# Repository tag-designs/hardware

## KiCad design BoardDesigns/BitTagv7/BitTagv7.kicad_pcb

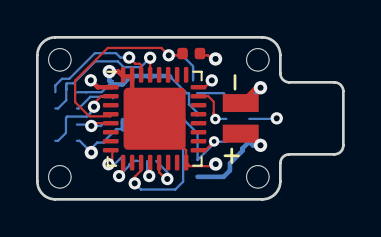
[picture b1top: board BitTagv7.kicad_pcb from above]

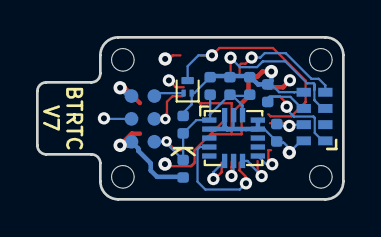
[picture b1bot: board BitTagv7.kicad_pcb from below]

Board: 4 copper layers, 17.0 x 9.0 mm, 18 parts (11 on the bottom side), 16 nets.

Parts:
C402, C403, C501, C502, C503: 0.1uf; C_0402_1005Metric
C404: 4.7uf; C_0402_1005Metric
D401: D; D_0402_1005Metric
J201: CONN_02X04; tagpoints6
J301, J302, J303, J304: Conn_01x01; taghole1.25mm
J401: CONN_01X02; MS621
Q501: Q_NPN_BEC; SOT-883
R1: 10k; R_0402_1005Metric
U302: stm32l432; QFN-32-1EP_5x5mm_P0.5mm_EP3.45x3.45mm
U405: adxl362; ADXL362
U501: RV-3028-C7; RV-8803-C7

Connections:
/SCL: U302.29, U501.3
/SDA: U302.30, U501.4
/clkout: U302.2, U501.1
ACCEL_CS: U302.9, U405.8
GND: C402.2, C403.2, C404.2, C501.2, C502.2, C503.2, J201.6, J401.2, Q501.2, R1.2, U302.16, U302.31, U302.32, U302.33, U405.2, U405.12, U405.13, U405.15, U405.16, U501.5, U501.8
unnamed: C502.1, Q501.3, U302.4
unnamed: R1.1, U501.6
RST: J201.5, Q501.1
SENS_MISO: U302.12, U405.7
SENS_MOSI: U302.13, U405.6
SENS_SCLK: U302.11, U405.4
SWCLK: J201.4, U302.24
SWDIO: J201.3, U302.23
VBAT: D401.2, J201.2, J401.1
VIN: C402.1, C403.1, C404.1, C501.1, C503.1, D401.1, J201.1, U302.1, U302.5, U302.17, U405.1, U405.14, U501.7
WKUP4: U302.8, U405.9

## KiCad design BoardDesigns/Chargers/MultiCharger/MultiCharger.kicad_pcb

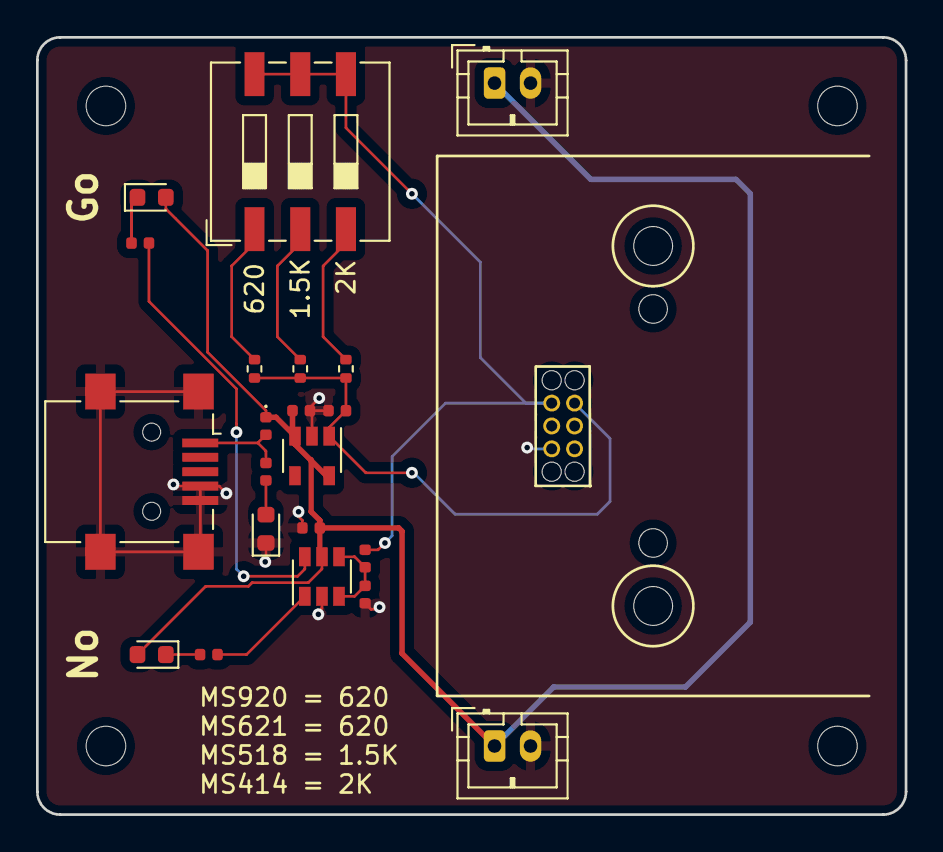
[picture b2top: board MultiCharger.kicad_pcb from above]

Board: 2 copper layers, 48.3 x 43.2 mm, 26 parts (0 on the bottom side), 14 nets.

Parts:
C101: 0.1uF; C_0402_1005Metric
C106: 1uF; C_0402_1005Metric
C107: 2.2uF; C_0402_1005Metric
D101: No Go; LED_0603_1608Metric
D102: LED; LED_0603_1608Metric
D103: Go; LED_0603_1608Metric
D104: D; D_0402_1005Metric
J101, J102: Conn_01x02; JST_PH_B2B-PH-K_1x02_P2.00mm_Vertical
J103: Tagbase; 6pin_tagpoints_new_offset
J104: USB_B_Mini; USB_Mini-B_Lumberg_2486_01_Horizontal
MK101, MK102, MK103, MK104: Mounting_Hole; MountingHole_2.2mm_M2
R1: 620; R_0402_1005Metric
R101, R102, R105: 1K; R_0402_1005Metric
R103: 910K; R_0402_1005Metric
R104: 130K; R_0402_1005Metric
R106: 1500; R_0402_1005Metric
R107: 2000; R_0402_1005Metric
SW101: SW_DIP_x03; SW_DIP_SPSTx03_Slide_9.78x9.8mm_W8.61mm_P2.54mm
U101: TLV6700; SOT-23-6
U106: TLV70A933_SOT23-5; SOT-23-5

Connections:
+3V3: C107.1, J103.5, R1.2, R106.2, R107.2, U106.1
/VIN: C101.1, C106.1, D101.2, D103.2, D104.1, J101.1, J102.1, U101.5, U106.3, U106.5
/Vsense: R103.2, R104.1, U101.3, U101.4
GND: C101.2, C106.2, C107.2, D102.1, J101.2, J102.2, J103.2, J104.4, J104.5, J104.6, R104.2, U101.2, U106.2
unnamed: D101.1, R101.2
unnamed: D102.2, R102.2
unnamed: D103.1, R105.2
unnamed: D104.2, J104.1, R102.1
unnamed: R1.1, SW101.1
unnamed: R101.1, U101.1
unnamed: R105.1, U101.6
unnamed: R106.1, SW101.2
unnamed: R107.1, SW101.3
TAG_VBAT: J103.6, R103.1, SW101.4, SW101.5, SW101.6

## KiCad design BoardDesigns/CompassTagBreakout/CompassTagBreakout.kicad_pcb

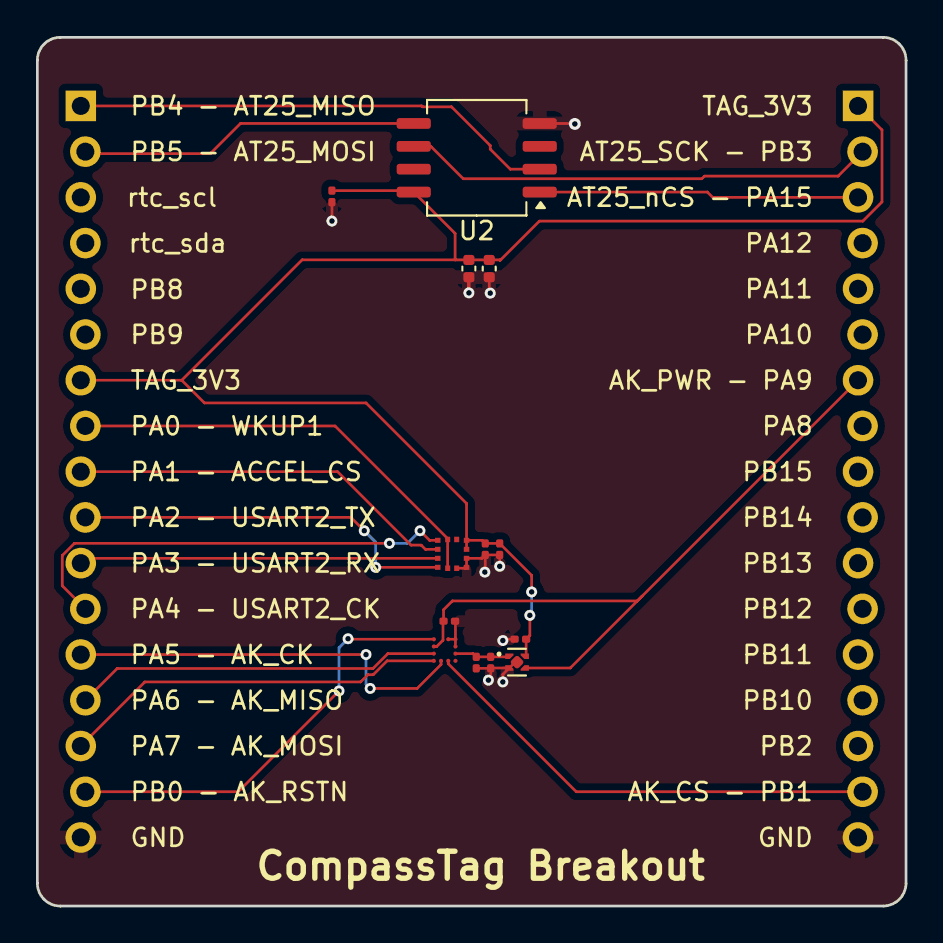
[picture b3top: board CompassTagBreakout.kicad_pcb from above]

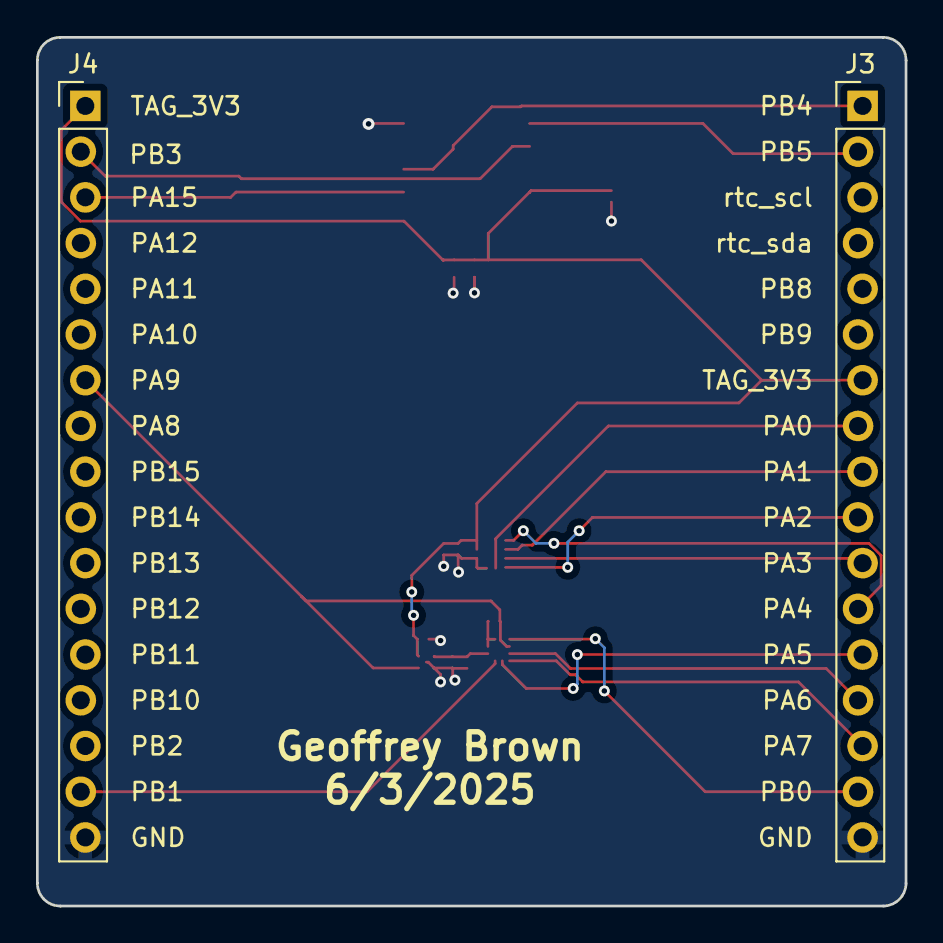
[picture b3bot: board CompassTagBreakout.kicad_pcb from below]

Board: 2 copper layers, 48.3 x 48.3 mm, 15 parts (2 on the bottom side), 18 nets.

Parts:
C3, C4, C9: 1uf; C_0201_0603Metric
C5, C6, C7, C8: 0.1uf; C_0201_0603Metric
C10, C11: 22uf; C_0402_1005Metric
J3, J4: Conn_01x17; PinHeader_1x17_P2.54mm_Vertical_Staggered
U1: TPS7A2018PDQN; Texas_X2SON-4_1x1mm_P0.65mm
U2: AT25XE321; SO-8_5.3x6.2mm_P1.27mm
U3: AK09940A; AK09940a
U4: LIS2DU12TR; LGA-12L_LIS2DU12_STM

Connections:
+1V8: C4.1, C5.1, U1.1 (OUT), U3.B1 (VDD)
/ACCEL_CS: J3.9, U4.2 (CS)
/AK_CK: J3.13, U3.A3 (SCL/SK)
/AK_CS: J4.16, U3.A2 (CSB)
/AK_MISO: J3.14, U3.B4 (SO)
/AK_MOSI: J3.15, U3.A4 (SDA/SI)
/AK_PWR: C6.1, J4.7, U1.3 (EN), U3.C4 (VOD)
/AK_RSTN: J3.16, U3.D4 (RSTN)
/AT25_MISO: J3.1, U2.2 (SIO1)
/AT25_MOSI: J3.2, U2.5 (SIO0)
/AT25_SCK: J4.2, U2.6 (SCLK)
/AT25_nCS: J4.3, U2.1 (nCS)
/TAG_3V3: C3.1, C7.1, C8.1, C9.1, C10.1, C11.1, J3.7, J4.1, U1.4 (IN), U2.8 (VCC), U4.9 (VDD), U4.10 (VDD_IO)
/USART2_CK: J3.12, U4.1 (SCL/SPC)
/USART2_RX: J3.11, U4.3 (SDO/SA0)
/USART2_TX: J3.10, U4.4 (SDA/SDI/SDO)
/WKUP1: J3.8, U4.5 (NC), U4.12 (INT1)
GND: C3.2, C4.2, C5.2, C6.2, C7.2, C8.2, C9.2, C10.2, C11.2, J3.17, J4.17, U1.2 (GND), U1.5 (Pad), U2.4 (GND), U3.C1 (VSS), U3.D1 (CAD0), U3.D2 (CAD1), U4.6 (GND), U4.7 (RES), U4.8 (GND)

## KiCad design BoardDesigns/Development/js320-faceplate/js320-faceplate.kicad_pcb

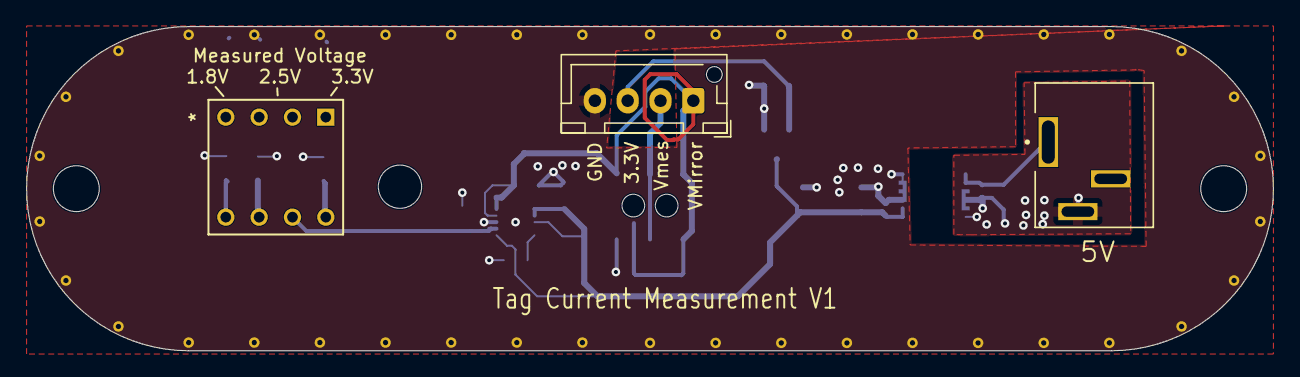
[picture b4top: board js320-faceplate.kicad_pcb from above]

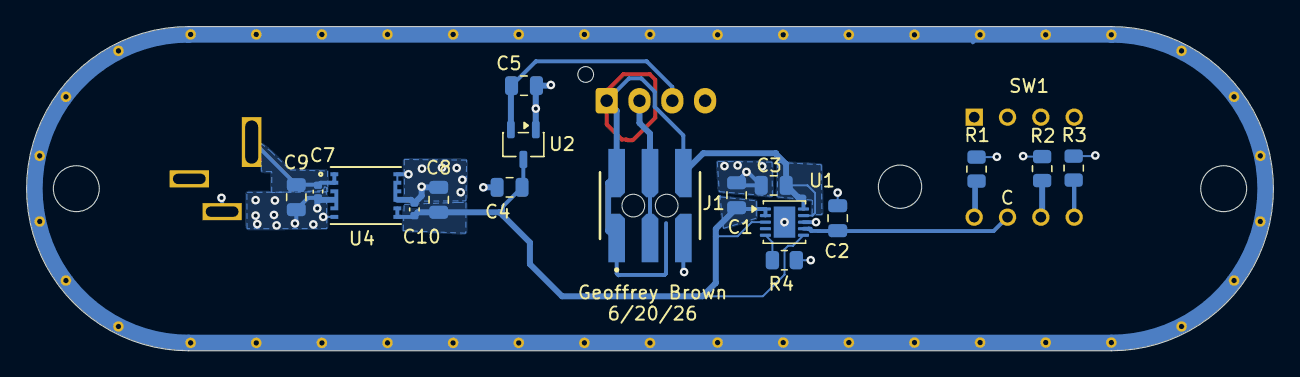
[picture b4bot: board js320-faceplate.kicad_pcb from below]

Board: 2 copper layers, 95.0 x 24.7 mm, 20 parts (16 on the bottom side), 12 nets.

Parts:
C1, C4, C5: 4.7uf; C_0805_2012Metric
C2: 470nf; C_0805_2012Metric
C3, C9: 10uf; C_0805_2012Metric
C7, C10: 22nf; C_0402_1005Metric
C8: 22uf; C_0805_2012Metric
J1: JS220
J3: Conn_01x04_Socket; JST_XH_B4B-XH-AM_1x04_P2.50mm_Vertical
J4: 54-00286; TENSILITY_54-00286
R1: 18k; R_0805_2012Metric
R2: 24k; R_0805_2012Metric
R3: 33k; R_0805_2012Metric
R4: 1k; R_0805_2012Metric
SW1: SS-10-23NPE; SS-10-23-NP_NDC
U1: LT3045xDD; DFN-10-1EP_3x3mm_P0.5mm_EP1.65x2.38mm
U2: XC6206PxxxMR; SOT-23-3
U4: PUCC33420RAQR; VSON-FCRLF12_RAQ_TEX

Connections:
+3.3V: C5.1, J3.3, U2.2 (VO)
/VINP: C7.1, C9.1, J4.A, U4.1 (EN/FLT), U4.2 (VINP)
/Vmeasure: J1.3 (I-), J1.4 (I-), J3.2
/Vprog: C3.1, J1.1 (I+), J1.2 (I+), J1.6 (V+), J3.1, U1.9 (OUTS), U1.10 (OUT)
/sens: C2.1, SW1.CB, U1.7 (SET)
/vin: C1.1, C4.1, C8.1, C10.1, U1.1 (IN), U1.2 (IN), U1.3 (EN/UV), U1.6 (PGFB), U2.3 (VI), U4.7 (SEL), U4.8 (VCC)
GND: C1.2, C2.2, C3.2, C4.2, C5.2, C8.2, C10.2, J1.5 (V-), J1.7 (SHIELD), J3.4, R1.2, R2.2, R3.2, R4.1, U1.8 (GND), U1.11 (GND), U2.1 (GND), U4.9 (GNDS), U4.10 (GNDS), U4.11 (GNDS), U4.12 (GNDS)
GNDPWR: C7.2, C9.2, J4.B, U4.3 (GNDP), U4.4 (GNDP), U4.5 (GNDP), U4.6 (GNDP)
unnamed: R1.1, SW1.1B
unnamed: R2.1, SW1.2B
unnamed: R3.1, SW1.3B
unnamed: R4.2, U1.5 (ILIM)

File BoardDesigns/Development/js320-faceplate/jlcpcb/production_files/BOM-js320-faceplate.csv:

Comment,Designator,Footprint,LCSC,Quantity
10uf,"C3,C9",C_0805_2012Metric,C15850,2
18k,R1,R_0805_2012Metric,C351602,1
1k,R4,R_0805_2012Metric,C17513,1
22nf,"C10,C7",C_0402_1005Metric,C1532,2
22uf,C8,C_0805_2012Metric,C45783,1
24k,R2,R_0805_2012Metric,C2692770,1
33k,R3,R_0805_2012Metric,C351577,1
4.7uf,"C1,C4,C5",C_0805_2012Metric,C1779,3
470nf,C2,C_0805_2012Metric,C13967,1
LT3045xDD,U1,DFN-10-1EP_3x3mm_P0.5mm_EP1.65x2.38mm,C514420,1
PUCC33420RAQR,U4,VSON-FCRLF12_RAQ_TEX,C46461551,1
XC6206PxxxMR,U2,SOT-23-3,C5148692,1

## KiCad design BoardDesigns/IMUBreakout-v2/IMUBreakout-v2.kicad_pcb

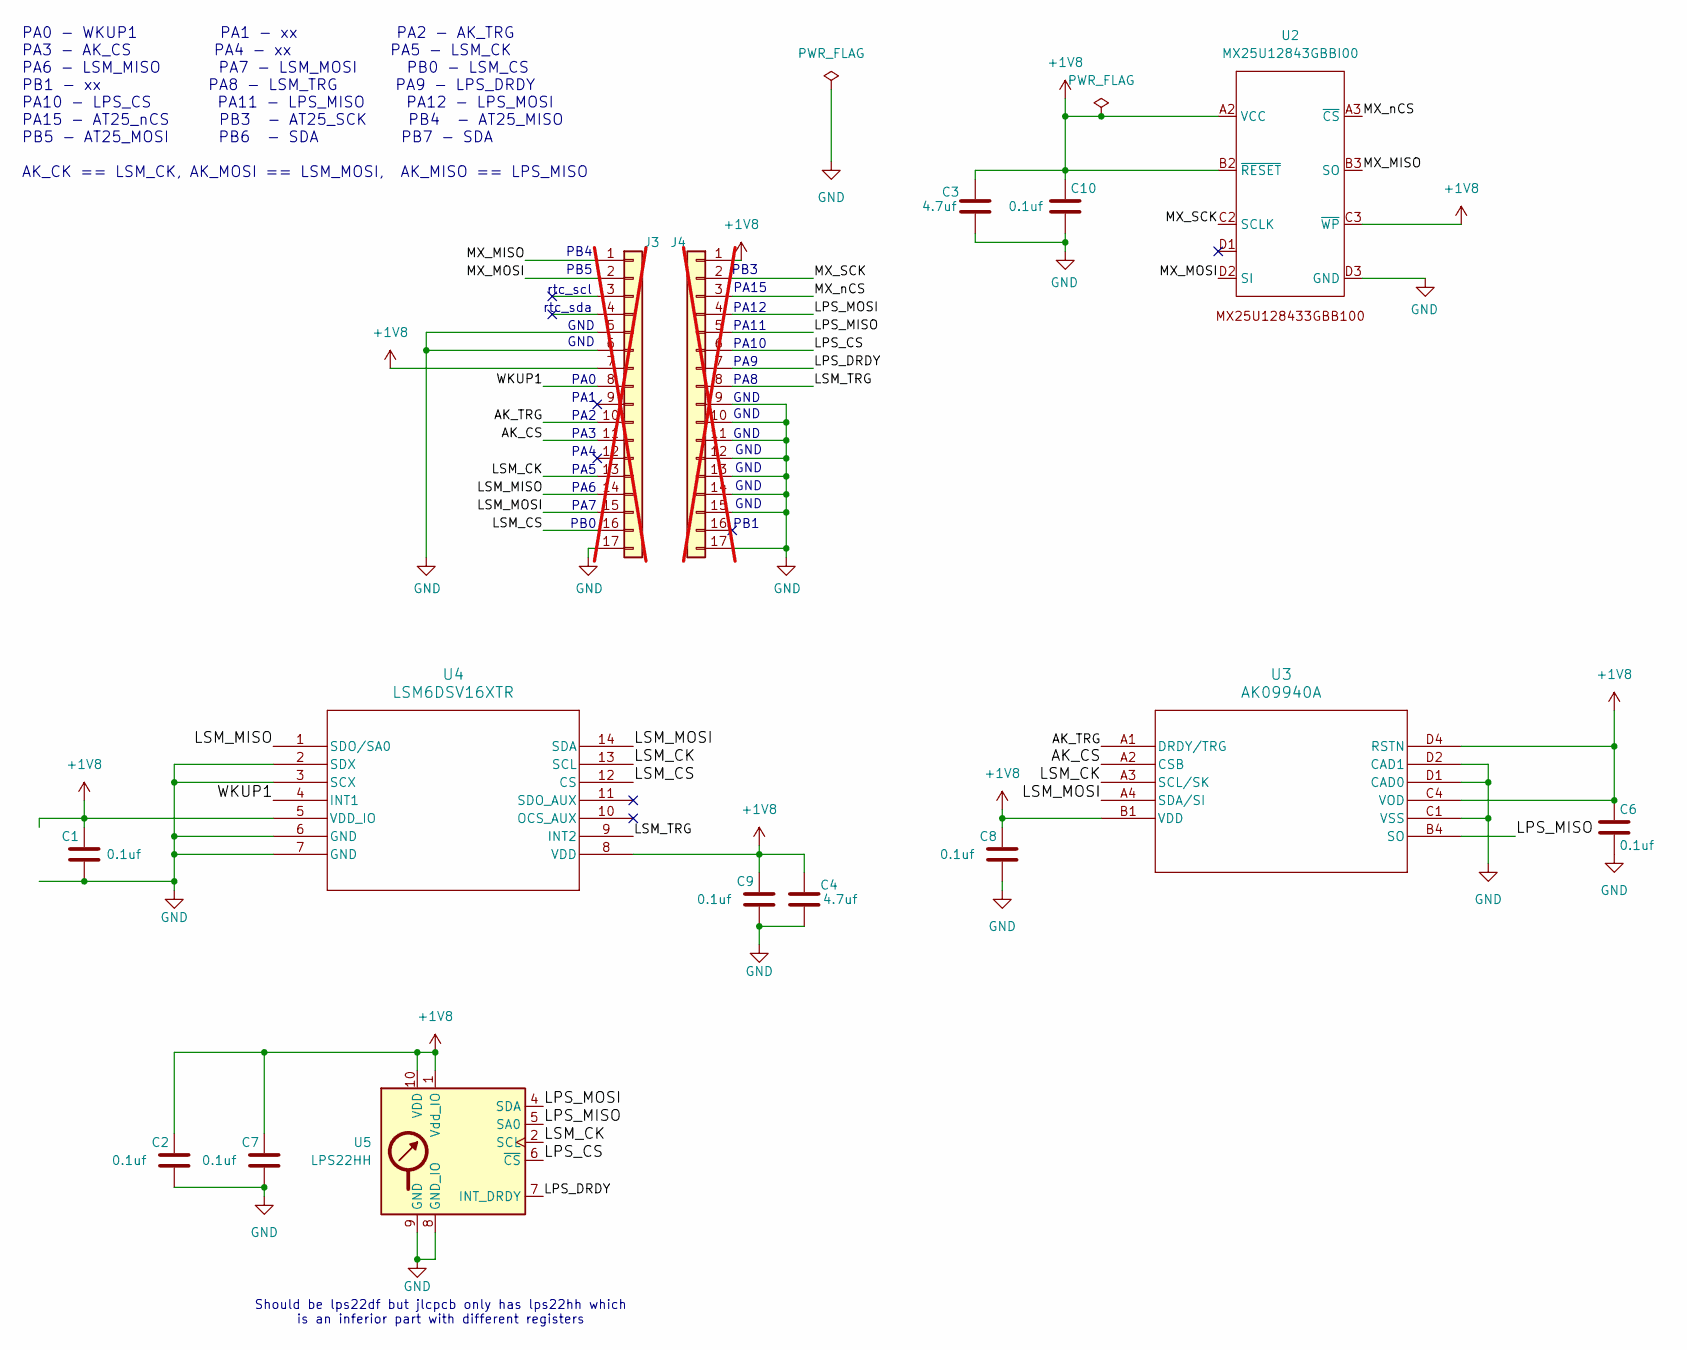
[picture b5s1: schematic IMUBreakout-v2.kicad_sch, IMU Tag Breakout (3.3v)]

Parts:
C1, C2, C6, C7, C8, C9, C10: 0.1uf; C_0603_1608Metric; MPN CC0603KRX7R9BB104; LCSC C14663
C3, C4: 4.7uf; C_0603_1608Metric; MPN CL10A475KO8NNNC; LCSC C19666
J3, J4: Conn_01x17; PinHeader_1x17_P2.54mm_Vertical_Staggered; not fitted
U2: MX25U12843GBBI00; IC_MX25U12843GBBI00; MPN MX25U12843GBBI00; LCSC C7316586
U3: AK09940A; AK09940a; MPN AK09940A; LCSC C6794828
U4: LSM6DSV16XTR; LGA-14_3x2.5mm_P0.5mm_LayoutBorder3x4y; MPN LSM6DSV; LCSC C5267406
U5: LPS22HH; ST_HLGA-10_2x2mm_P0.5mm_LayoutBorder3x2y; MPN LPS22HH; LCSC C2827824

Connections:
+1V8: C1.1, C2.1, C3.1, C4.1, C6.1, C7.1, C8.1, C9.1, C10.1, J3.7, J4.1, U2.A2 (VCC), U2.B2 (~RESET), U2.C3 (~WP), U3.B1 (VDD), U3.C4 (VOD), U3.D4 (RSTN), U4.5 (VDD_IO), U4.8 (VDD), U5.1 (Vdd_IO), U5.10 (VDD)
/AK_CS: J3.11, U3.A2 (CSB)
/AK_TRG: J3.10, U3.A1 (DRDY/TRG)
/LPS_CS: J4.6, U5.6 (~CS)
/LPS_DRDY: J4.7, U5.7 (INT_DRDY)
/LPS_MISO: J4.5, U3.B4 (SO), U5.5 (SA0)
/LPS_MOSI: J4.4, U5.4 (SDA)
/LSM_CK: J3.13, U3.A3 (SCL/SK), U4.13 (SCL), U5.2 (SCL)
/LSM_CS: J3.16, U4.12 (CS)
/LSM_MISO: J3.14, U4.1 (SDO/SA0)
/LSM_MOSI: J3.15, U3.A4 (SDA/SI), U4.14 (SDA)
/LSM_TRG: J4.8, U4.9 (INT2)
/MX_MISO: J3.1, U2.B3 (SO)
/MX_MOSI: J3.2, U2.D2 (SI)
/MX_SCK: J4.2, U2.C2 (SCLK)
/MX_nCS: J4.3, U2.A3 (~CS)
/WKUP1: J3.8, U4.4 (INT1)
GND: C1.2, C2.2, C3.2, C4.2, C6.2, C7.2, C8.2, C9.2, C10.2, J3.5, J3.6, J3.17, J4.9, J4.10, J4.11, J4.12, J4.13, J4.14, J4.15, J4.17, U2.D3 (GND), U3.C1 (VSS), U3.D1 (CAD0), U3.D2 (CAD1), U4.2 (SDX), U4.3 (SCX), U4.6 (GND), U4.7 (GND), U5.3 (GND), U5.8 (GND_IO), U5.9 (GND)

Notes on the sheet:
PA1
PA9
PA2
PA0
PA8
PA7
PA15
PA5
GND
PA4
PB3
PA6
Should be lps22df but jlcpcb only has lps22hh which is an inferior part with different registers
PA3
PB4
PA12
PB0
PA0 - WKUP1 PA1 - xx PA2 - AK_TRG PA3 - AK_CS PA4 - xx PA5 - LSM_CK PA6 - LSM_MISO PA7 - LSM_MOSI PB0 - LSM_CS PB1 - xx PA8 - LSM_TRG PA9 - LPS_DRDY PA10 - LPS_CS PA11 - LPS_MISO PA12 - LPS_MOSI PA15 - AT25_nCS PB3 - AT25_SCK PB4 - AT25_MISO PB5 - AT25_MOSI PB6 - SDA PB7 - SDA AK_CK == LSM_CK, AK_M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
PB5
PA10
rtc_sda
PA11
PB1
rtc_scl

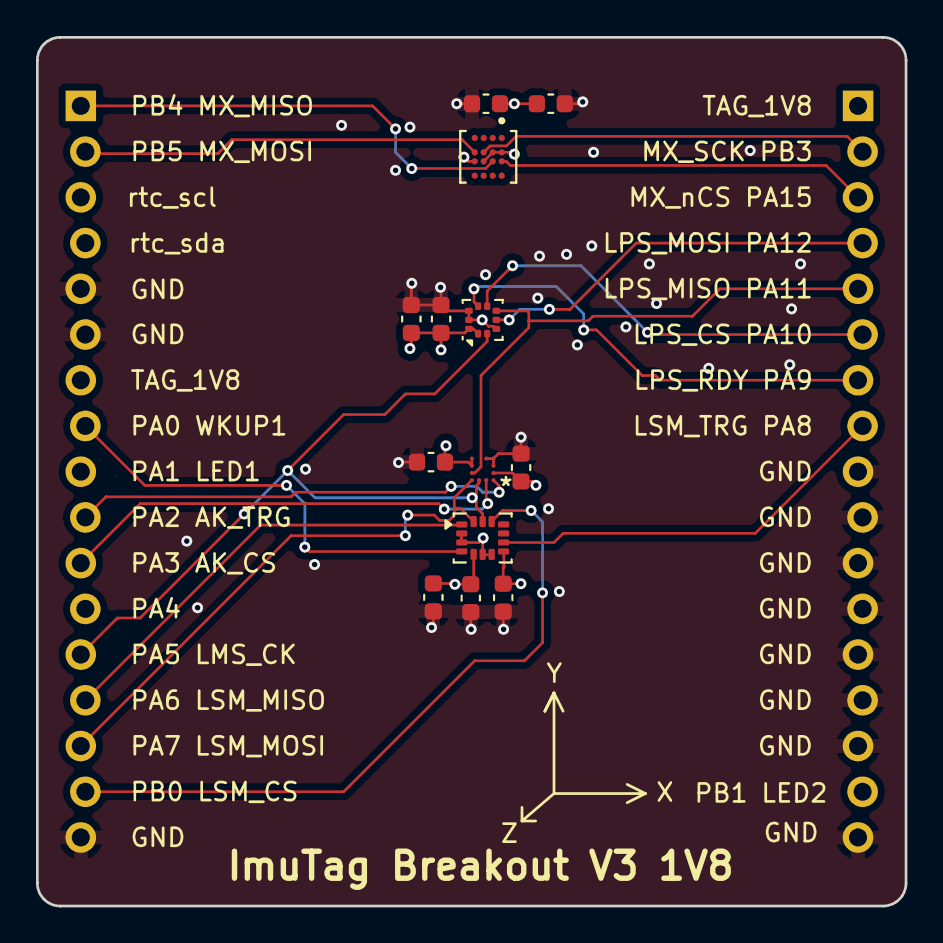
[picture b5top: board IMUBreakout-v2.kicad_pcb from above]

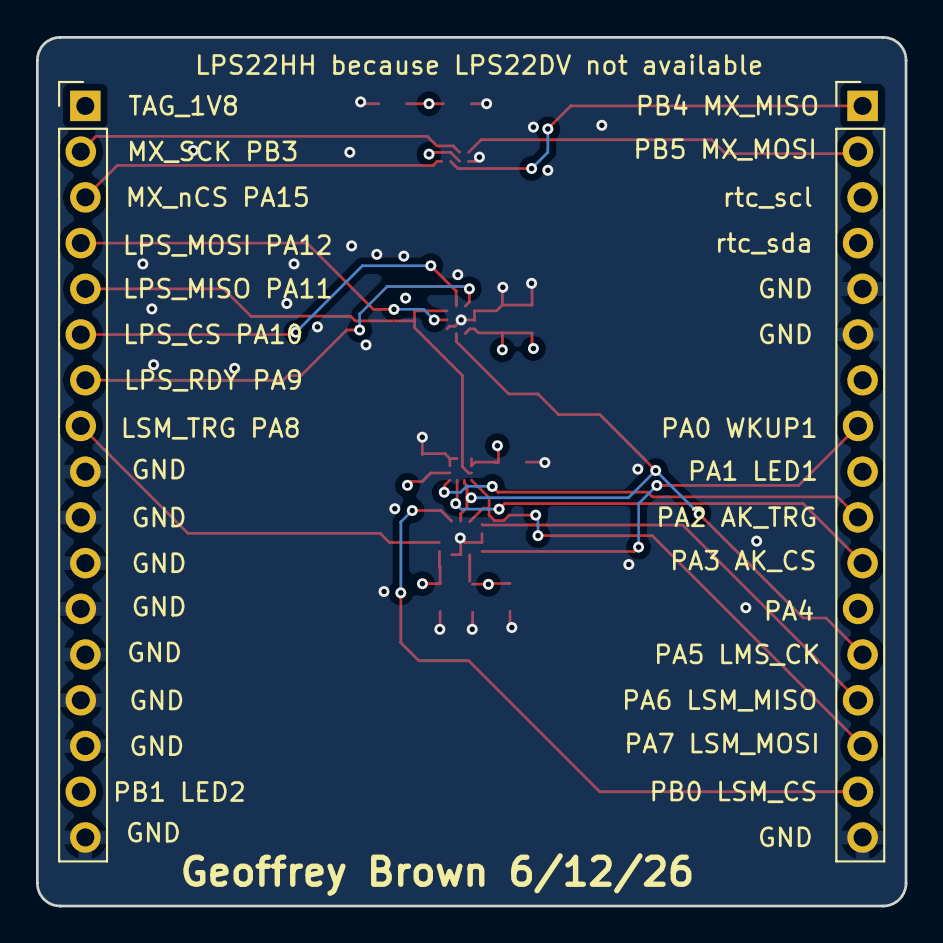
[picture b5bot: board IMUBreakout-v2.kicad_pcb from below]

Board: 4 copper layers, 48.3 x 48.3 mm, 15 parts (2 on the bottom side), 18 nets.

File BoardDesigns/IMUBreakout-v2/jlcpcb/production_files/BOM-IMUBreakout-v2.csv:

Comment,Designator,Footprint,LCSC,Quantity
0.1uf,"C1,C10,C2,C6,C7,C8,C9",C_0603_1608Metric,C14663,7
4.7uf,"C3,C4",C_0603_1608Metric,C19666,2
AK09940A,U3,AK09940a,C6794828,1
LPS22HH,U5,ST_HLGA-10_2x2mm_P0.5mm_LayoutBorder3x2y,C2827824,1
LSM6DSV16XTR,U4,LGA-14_3x2.5mm_P0.5mm_LayoutBorder3x4y,C5267406,1
MX25U12843GBBI00,U2,IC_MX25U12843GBBI00,C7316586,1

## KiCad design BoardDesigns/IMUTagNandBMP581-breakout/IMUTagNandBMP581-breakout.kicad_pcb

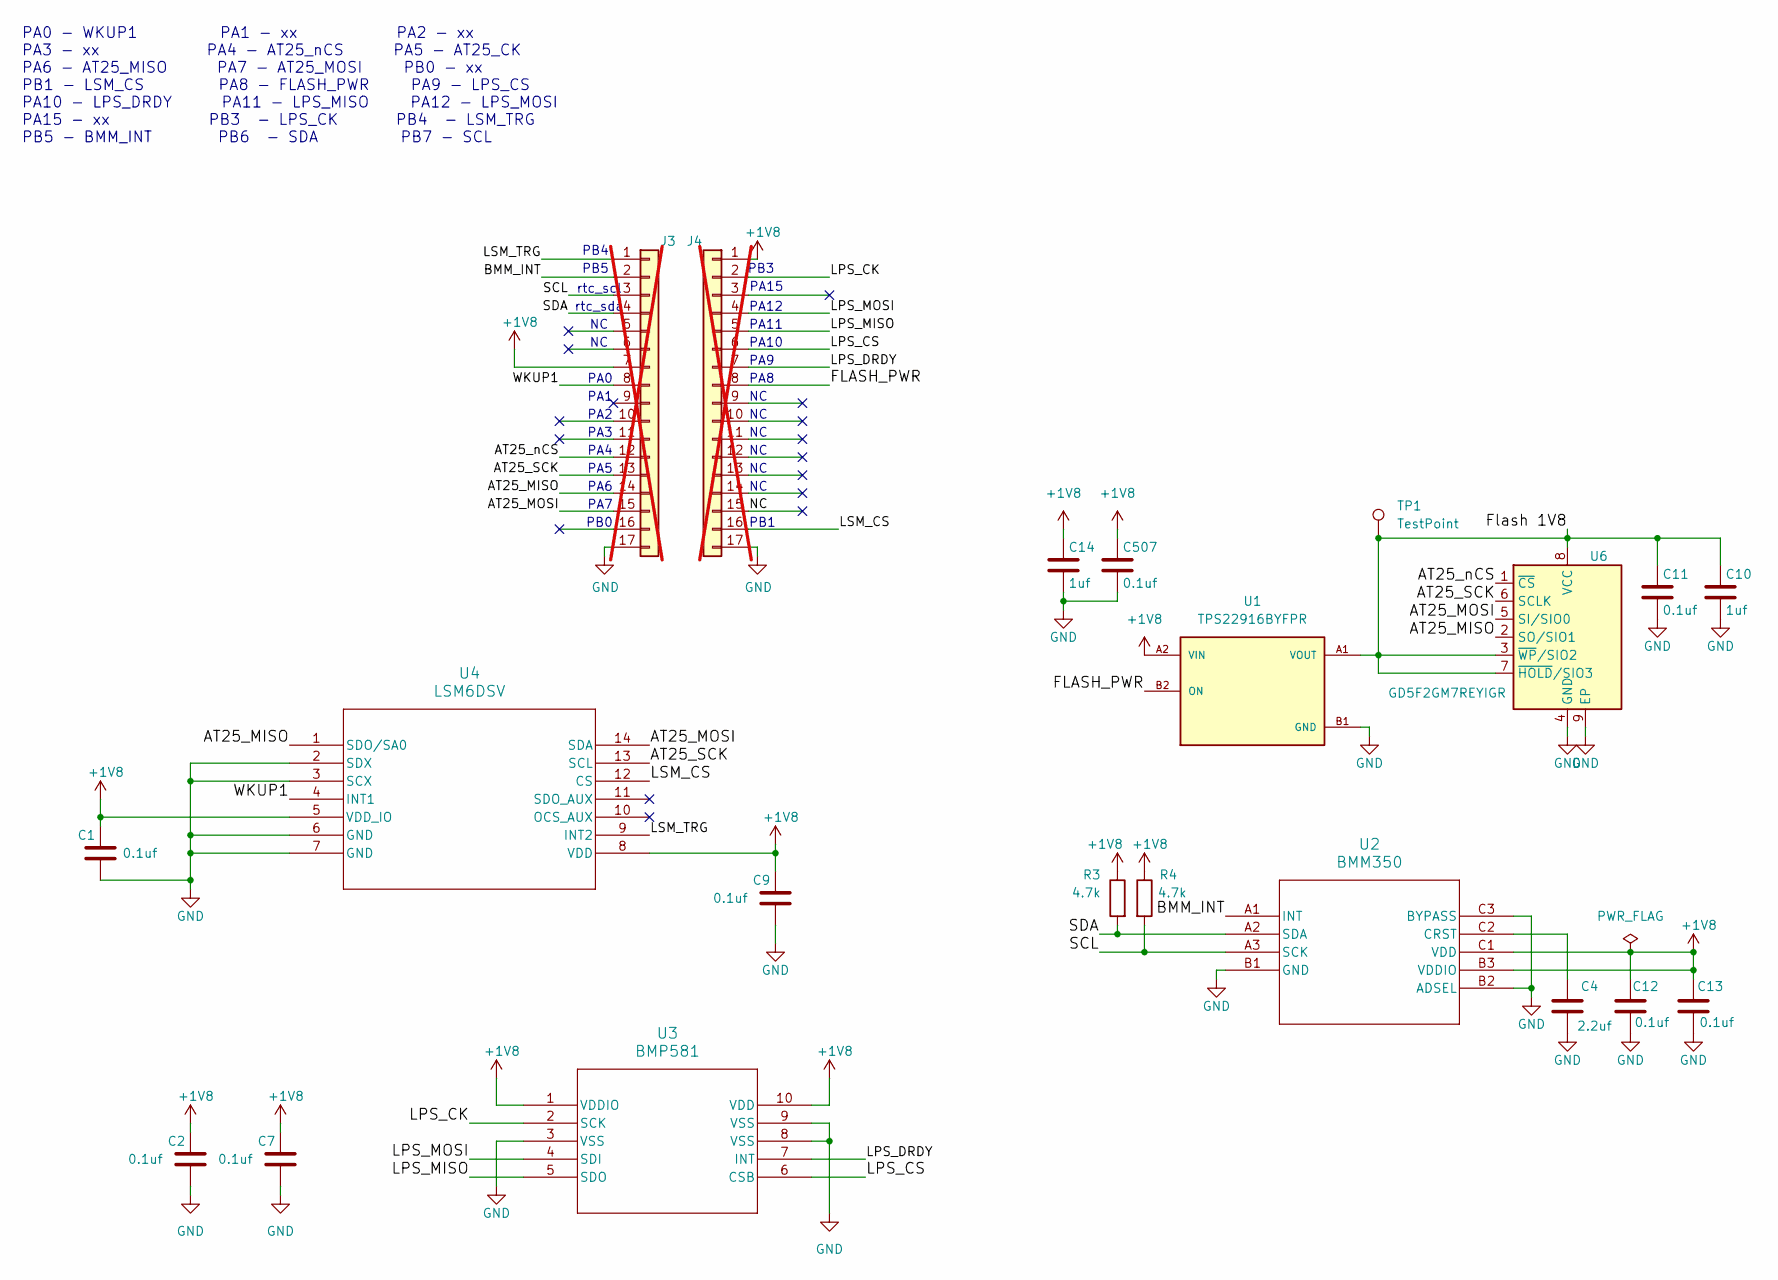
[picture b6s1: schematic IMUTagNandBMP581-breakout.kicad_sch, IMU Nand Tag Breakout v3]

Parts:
C1, C2, C7, C9, C11, C12, C13, C507: 0.1uf; C_0603_1608Metric; MPN CC0603KRX7R9BB104; LCSC C14663
C4: 2.2uf; C_0603_1608Metric; MPN GRM188R61H225KE11D; LCSC C162273
C10, C14: 1uf; C_0603_1608Metric; MPN CL10A105KB8NNNC; LCSC C15849
J3, J4: Conn_01x17; PinHeader_1x17_P2.54mm_Vertical_Staggered; not fitted
R3, R4: 4.7k; R_0603_1608Metric; MPN 0603WAF4701T5E; LCSC C23162
TP1: TestPoint; TestPoint_Pad_D2.0mm
U1: TPS22916BYFPR; IC_TPS22916BYFPR; PARTREV F; LCSC C2150095
U2: BMM350; BGA9_BMM350_BOS; MPN BMM350; LCSC C17225907
U3: BMP581; QFN10_BMP581_BOS; MPN BMP581; LCSC C5362283
U4: LSM6DSV; LGA14-L_2P59X3P1X0P5_STM; MPN LSM6DSV; LCSC C5267399
U6: GD5F2GM7REYIGR; WSON-8-1EP_8x6mm_P1.27mm_EP3.4x4.3mm; MPN GD5F2GM7REYIGR; LCSC C23706308

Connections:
+1V8: C1.1, C2.1, C7.1, C9.1, C12.1, C13.1, C14.1, C507.1, J3.7, J4.1, R3.1, R4.1, U1.A2 (VIN), U2.B3 (VDDIO), U2.C1 (VDD), U3.1 (VDDIO), U3.10 (VDD), U4.5 (VDD_IO), U4.8 (VDD)
/AT25_MISO: J3.14, U4.1 (SDO/SA0), U6.2 (SO/SIO1)
/AT25_MOSI: J3.15, U4.14 (SDA), U6.5 (SI/SIO0)
/AT25_SCK: J3.13, U4.13 (SCL), U6.6 (SCLK)
/AT25_nCS: J3.12, U6.1 (~CS)
/BMM_INT: J3.2, U2.A1 (INT)
/FLASH_PWR: J4.8, U1.B2 (ON)
/Flash 1V8: C10.1, C11.1, TP1.1 (1_1), U1.A1 (VOUT), U6.3 (~WP/SIO2), U6.7 (~HOLD/SIO3), U6.8 (VCC)
/LPS_CK: J4.2, U3.2 (SCK)
/LPS_CS: J4.6, U3.6 (CSB)
/LPS_DRDY: J4.7, U3.7 (INT)
/LPS_MISO: J4.5, U3.5 (SDO)
/LPS_MOSI: J4.4, U3.4 (SDI)
/LSM_CS: J4.16, U4.12 (CS)
/LSM_TRG: J3.1, U4.9 (INT2)
/NC: J4.15
/SCL: J3.3, R4.2, U2.A3 (SCK)
/SDA: J3.4, R3.2, U2.A2 (SDA)
/WKUP1: J3.8, U4.4 (INT1)
GND: C1.2, C2.2, C4.2, C7.2, C9.2, C10.2, C11.2, C12.2, C13.2, C14.2, C507.2, J3.17, J4.17, U1.B1 (GND), U2.B1 (GND), U2.B2 (ADSEL), U2.C3 (BYPASS), U3.3 (VSS), U3.8 (VSS), U3.9 (VSS), U4.2 (SDX), U4.3 (SCX), U4.6 (GND), U4.7 (GND), U6.4 (GND), U6.9 (EP)
unnamed: C4.1, U2.C2 (CRST)

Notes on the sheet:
PA1
PA9
PA2
PA0
PA8
PA7
PA15
PA5
PA4
PB3
PA6
PA3
PA0 - WKUP1 PA1 - xx PA2 - xx PA3 - xx PA4 - AT25_nCS PA5 - AT25_CK PA6 - AT25_MISO PA7 - AT25_MOSI PB0 - xx PB1 - LSM_CS PA8 - FLASH_PWR PA9 - LPS_CS PA10 - LPS_DRDY PA11 - LPS_MISO PA12 - LPS_MOSI PA15 - xx PB3 - LPS_CK PB4 - LSM_TRG PB5 - BMM_INT PB6 - SDA PB7 - SCL
PB4
PA12
PB0
PB5
PA10
rtc_sda
PA11
PB1
rtc_scl

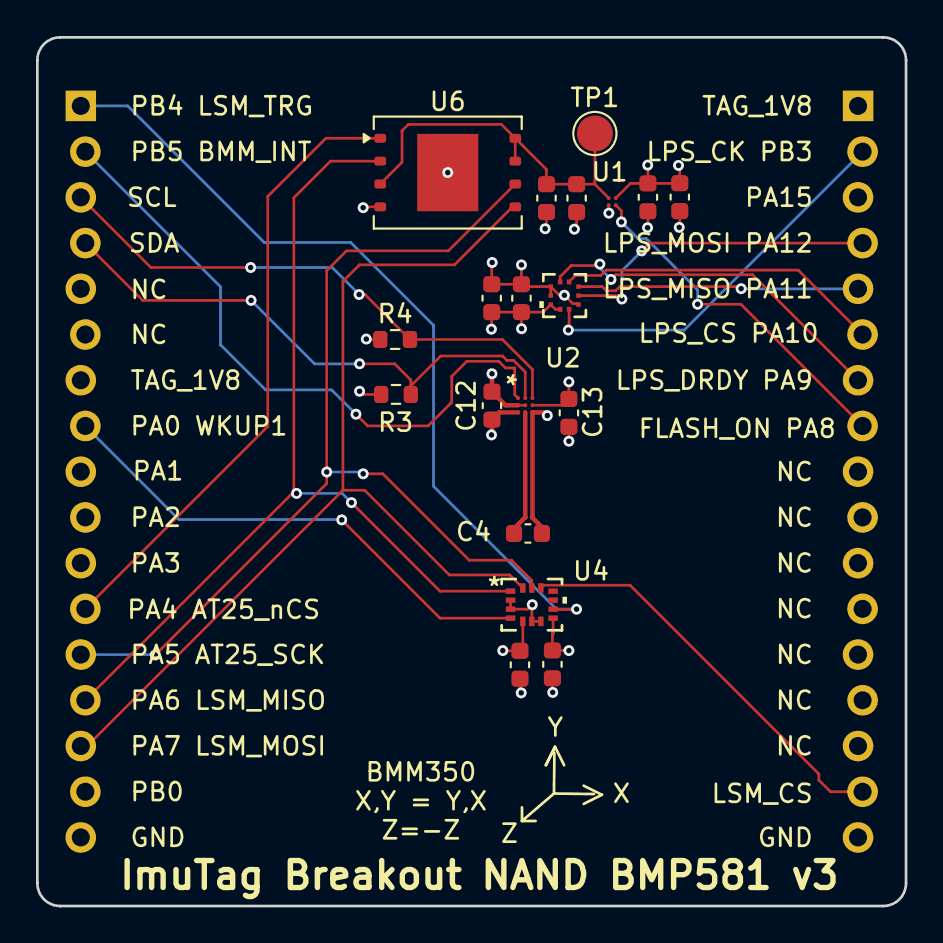
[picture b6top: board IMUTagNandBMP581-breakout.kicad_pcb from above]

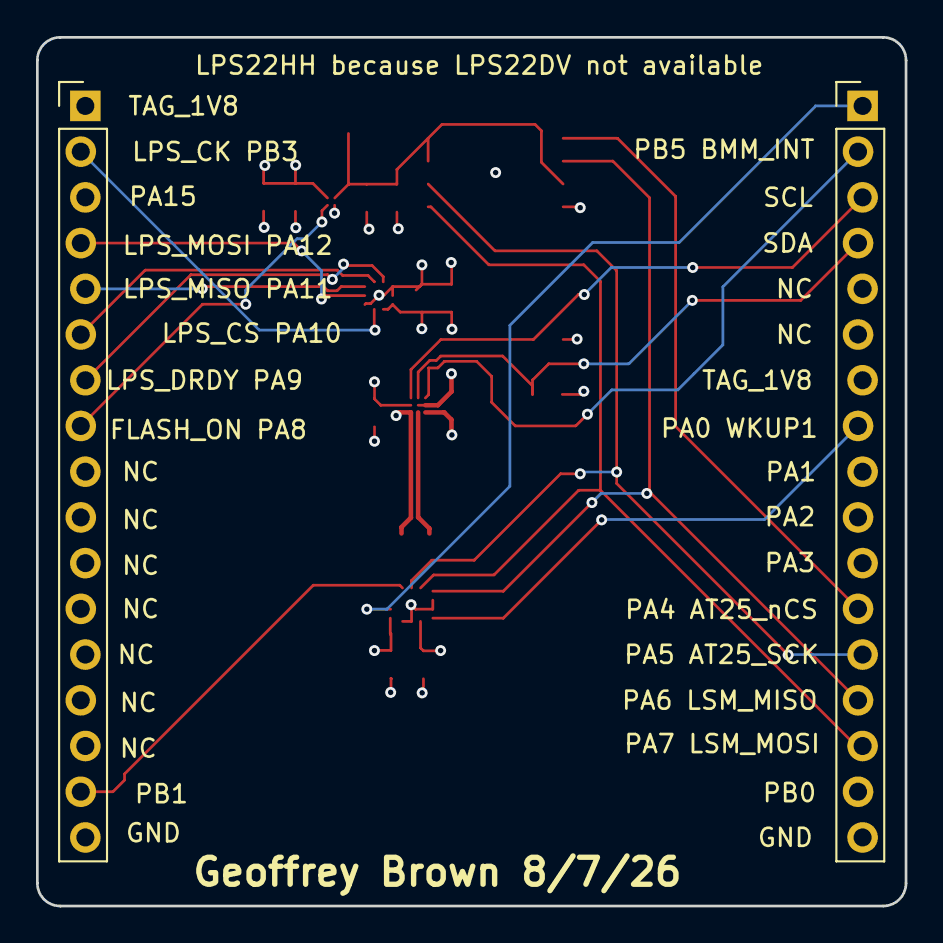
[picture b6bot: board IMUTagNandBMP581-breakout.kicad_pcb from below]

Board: 4 copper layers, 48.3 x 48.3 mm, 21 parts (2 on the bottom side), 20 nets.

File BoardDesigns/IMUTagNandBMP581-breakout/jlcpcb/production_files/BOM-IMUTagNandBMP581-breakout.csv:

Comment,Designator,Footprint,LCSC,Quantity
0.1uf,"C1,C11,C12,C13,C2,C507,C7,C9",C_0603_1608Metric,C14663,8
1uf,"C10,C14",C_0603_1608Metric,C15849,2
2.2uf,C4,C_0603_1608Metric,C162273,1
4.7k,"R3,R4",R_0603_1608Metric,C23162,2
BMM350,U2,BGA9_BMM350_BOS,C17225907,1
BMP581,U3,QFN10_BMP581_BOS,C5362283,1
GD5F1GQ5REYIGR,U6,WSON-8-1EP_8x6mm_P1.27mm_EP3.4x4.3mm,C2927042,1
LSM6DSV,U4,LGA14-L_2P59X3P1X0P5_STM,C5267406,1
TPS22916BYFPR,U1,IC_TPS22916BYFPR,C2150095,1
